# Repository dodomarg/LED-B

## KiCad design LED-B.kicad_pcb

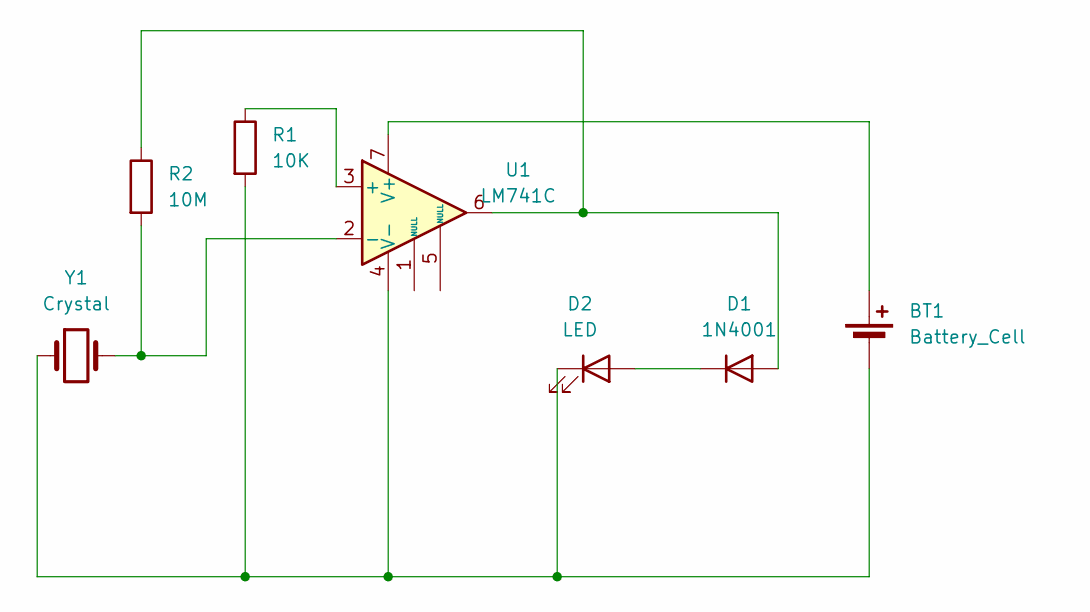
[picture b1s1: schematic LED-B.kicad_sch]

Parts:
BT1: Battery_Cell; BAT_BH800S
D1: 1N4001; D_DO-41_SOD81_P10.16mm_Horizontal
D2: LED; LED_D3.0mm
R1: 10K; R_Axial_DIN0207_L6.3mm_D2.5mm_P10.16mm_Horizontal
R2: 10M; R_Axial_DIN0207_L6.3mm_D2.5mm_P10.16mm_Horizontal
U1: LM741C; DIP-8_W7.62mm
Y1: Crystal; PinHeader_1x02_P2.54mm_Vertical

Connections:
unnamed: BT1.1 (+), U1.7 (V+)
unnamed: BT1.2 (-), D2.1 (K), R1.2, U1.4 (V-), Y1.1
unnamed: D1.2 (A), R2.1, U1.6
unnamed: D1.1 (K), D2.2 (A)
unnamed: R1.1, U1.3 (+)
unnamed: R2.2, U1.2 (-), Y1.2

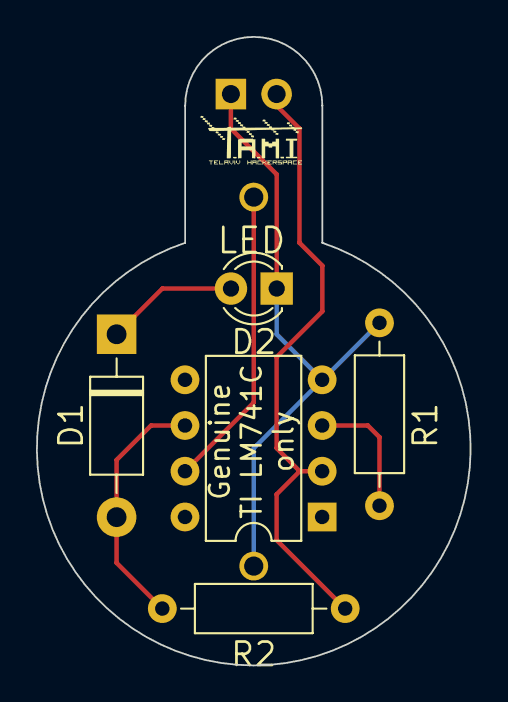
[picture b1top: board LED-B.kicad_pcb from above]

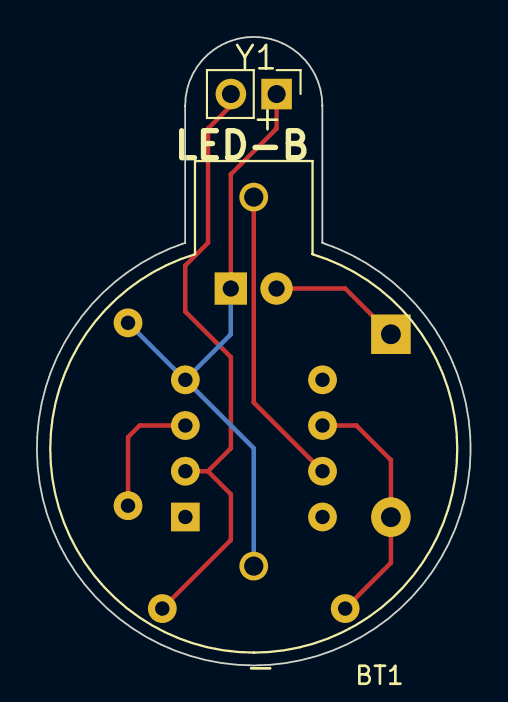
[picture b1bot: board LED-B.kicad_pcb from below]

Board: 2 copper layers, 24.1 x 34.9 mm, 7 parts (2 on the bottom side), 6 nets.
